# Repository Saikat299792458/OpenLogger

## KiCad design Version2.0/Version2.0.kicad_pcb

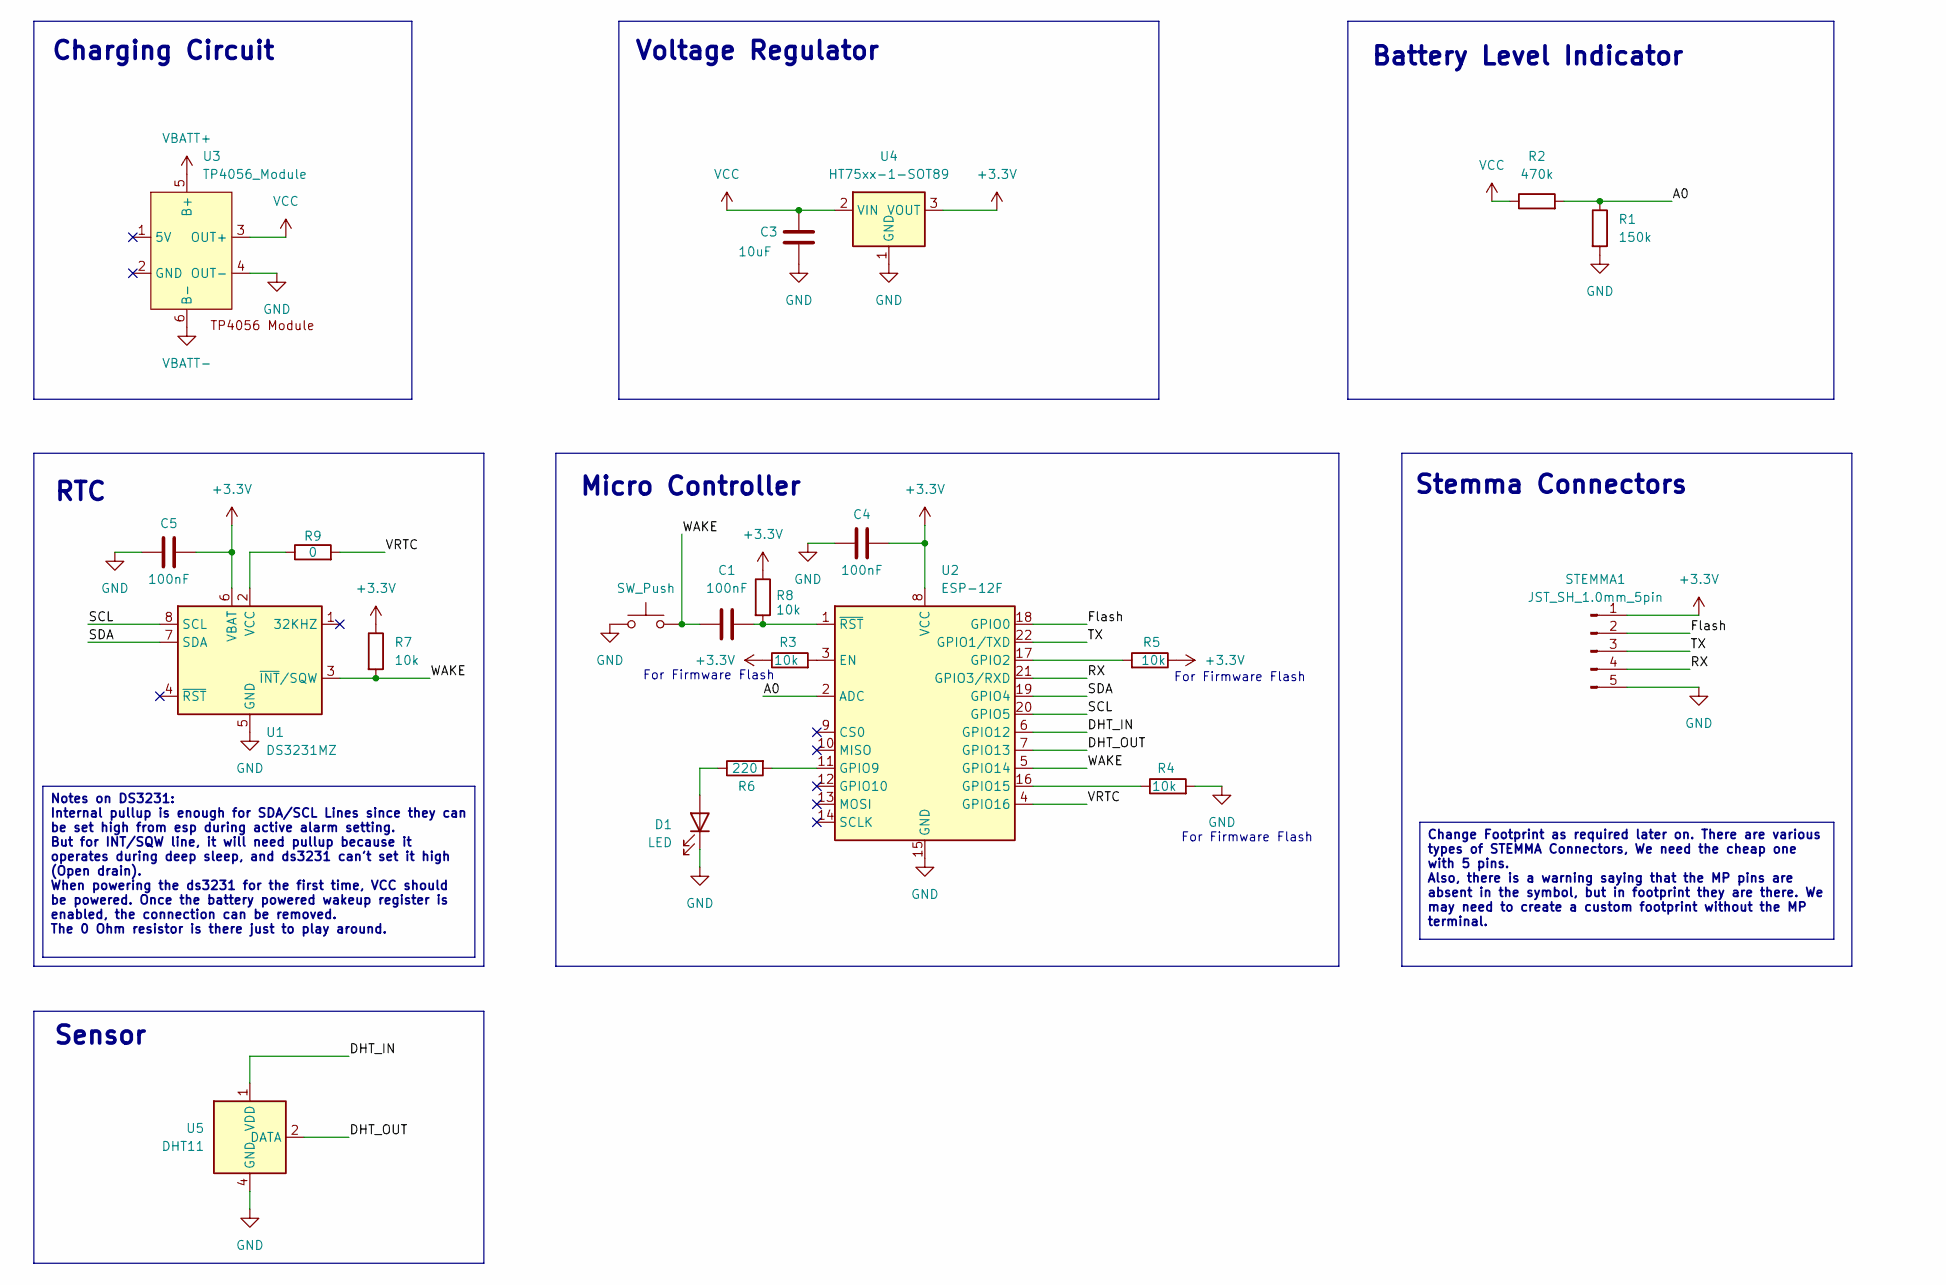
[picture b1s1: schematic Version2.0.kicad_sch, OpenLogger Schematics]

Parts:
C1, C4, C5: 100nF; C_0805_2012Metric
C3: 10uF; C_1210_3225Metric
D1: LED; LED_0805_2012Metric
R1: 150k; R_0805_2012Metric
R2: 470k; R_0805_2012Metric
R3, R4, R5, R7, R8: 10k; R_0805_2012Metric
R6: 220; R_0805_2012Metric
R9: 0; R_0805_2012Metric
STEMMA1: JST_SH_1.0mm_5pin; JST_XH_B5B-XH-A_1x05_P2.50mm_Vertical
SW1: SW_Push; SW_PUSH_6mm
U1: DS3231MZ; SOIC-8_3.9x4.9mm_P1.27mm
U2: ESP-12F; ESP-12E
U3: TP4056_Module; TP4056-18650
U4: HT75xx-1-SOT89; SOT-89-3
U5: DHT11; Aosong_DHT11_5.5x12.0_P2.54mm

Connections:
+3.3V: C4.2, C5.2, R3.1, R5.1, R7.1, R8.1, STEMMA1.1, U1.6 (VBAT), U2.8 (VCC), U4.3 (VOUT); also elsewhere on the board
/A0: R1.1, R2.2, U2.2 (ADC)
/DHT_IN: U2.6 (GPIO12), U5.1 (VDD)
/DHT_OUT: U2.7 (GPIO13), U5.2 (DATA)
/Flash: STEMMA1.2, U2.18 (GPIO0)
/RX: STEMMA1.4, U2.21 (GPIO3/RXD)
/SCL: U1.8 (SCL), U2.20 (GPIO5)
/SDA: U1.7 (SDA), U2.19 (GPIO4)
/TX: STEMMA1.3, U2.22 (GPIO1/TXD)
/VRTC: R9.2, U2.4 (GPIO16)
/WAKE: C1.1, R7.2, SW1.2, U1.3 (~INT/SQW), U2.5 (GPIO14)
GND: C3.2, C4.1, C5.1, D1.1 (K), R1.2, R4.2, STEMMA1.5, SW1.1, U1.5 (GND), U2.15 (GND), U3.4 (OUT-), U4.1 (GND), U5.4 (GND); also elsewhere on the board
unnamed: D1.2 (A), R6.1
unnamed: R9.1, U1.2 (VCC)
unnamed: R3.2, U2.3 (EN)
unnamed: R5.2, U2.17 (GPIO2)
unnamed: R6.2, U2.11 (GPIO9)
unnamed: R4.1, U2.16 (GPIO15)
unnamed: C1.2, R8.2, U2.1 (~RST)
VBATT+: U3.5 (B+)
VBATT-: U3.6 (B-)
VCC: C3.1, R2.1, U3.3 (OUT+), U4.2 (VIN)

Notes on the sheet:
Sensor
For Firmware Flash
Stemma Connectors
Micro Controller
Battery Level Indicator
Voltage Regulator
Charging Circuit
RTC
Notes on DS3231: Internal pullup is enough for SDA/SCL Lines since they can be set high from esp during active alarm setting. But for INT/SQW line, it will need pullup because it operates during deep sleep, and ds3231 can't set it high (Open drain). When powering the ds3231 for the first time, VCC 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
Change Footprint as required later on. There are various types of STEMMA Connectors, We need the cheap one with 5 pins. Also, there is a warning saying that the MP pins are absent in the symbol, but in footprint they are there. We may need to create a custom footprint without the MP terminal.

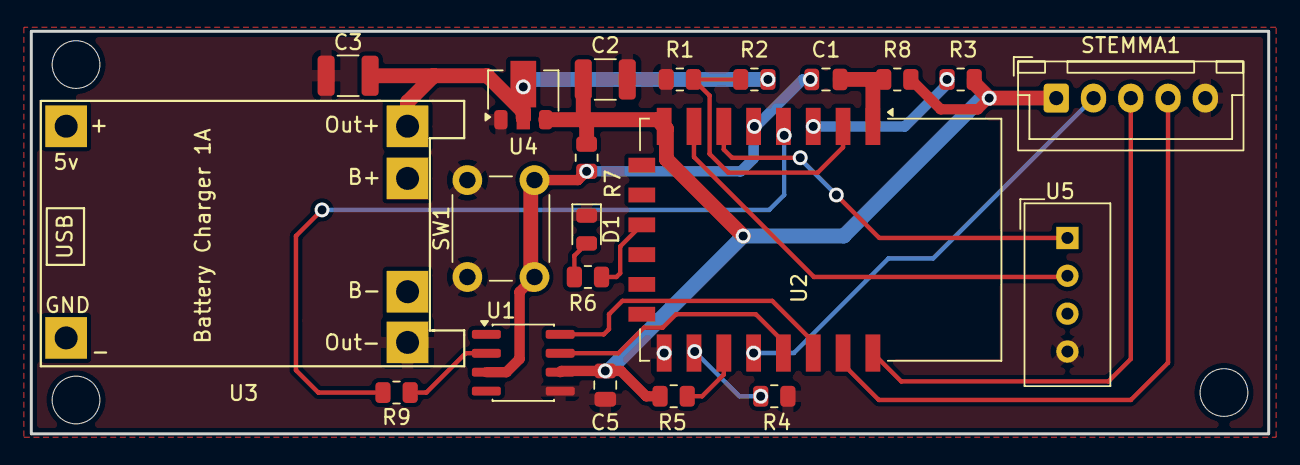
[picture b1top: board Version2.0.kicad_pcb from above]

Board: 2 copper layers, 83.0 x 27.0 mm, 21 parts (0 on the bottom side), 20 nets.

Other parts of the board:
C2: 100uF; C_1210_3225Metric

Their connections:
+3.3V: C2.1; also elsewhere on the board
GND: C2.2; also elsewhere on the board

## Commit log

2026-03-15 Circuit design and firmware creation
2026-03-23 design
2026-03-29 electrical design
2026-03-29 Schematics Update
2026-03-29 PCB Design
2026-03-30 PCB Complete
2026-03-30 casing
